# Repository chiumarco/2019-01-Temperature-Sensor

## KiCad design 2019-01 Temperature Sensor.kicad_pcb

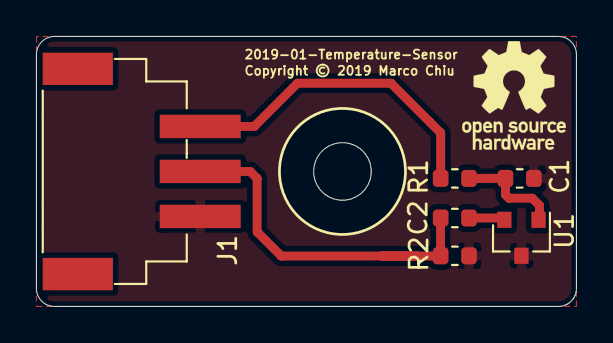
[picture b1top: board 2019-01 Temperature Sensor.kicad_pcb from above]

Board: 2 copper layers, 30.0 x 15.0 mm, 7 parts (0 on the bottom side), 5 nets.

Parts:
C1: 100n; C_0603_1608Metric
C2: 10n; C_0603_1608Metric
H1: MountingHole; MountingHole_3.2mm_M3
J1: Conn_01x03; JST_XH_B3B-XH-SM4-TB_1x03_P2.50mm_Horizontal_SMD
R1, R2: 10R; R_0603_1608Metric
U1: MCP9701AT; SOT-23

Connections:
GND: C1.2, C2.2, J1.3, U1.3
unnamed: C1.1, R1.1, U1.1
unnamed: C2.1, J1.2, R2.2
unnamed: J1.1, R1.2
unnamed: R2.1, U1.2

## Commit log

2019-09-21 Completed layout of the board.

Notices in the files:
2019-01 Temperature Sensor.kicad_pcb:
Copyright © 2019 Marco Chiu
